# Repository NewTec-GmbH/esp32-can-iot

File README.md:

# ESP CAN-Analyzer
An ESP32 based interface between CAN-Bus and IoT environments.

This project has the main objective of interfacing a CAN Bus with the user through the use of the Lawicel Protocol (also known as SLCAN). Lawicel represents CAN Frames as strings of ASCII Symbols which can be easily interpreted by the user of by the numerous applications available online. 

- [Technical Specifications](#Technical-Specifications)
	- [Software Requirements](#Software-Requirements)
	- [Hardware Requirements](#Hardware-Requirements)
	- [Extra/Optional Requirements](#Extra/Optional-Requirements)
- [Context](#Context)
- [Use Case](#Use-Case)
- [Potential Optimization](#Potential-Optimization)
- [Specialized Pages](#Specialized-Pages)

# Technical Specifications 
## Software Requirements
* Support Standard and Extended frame formats
* WiFi Mode Selection (AP or STA)
* Support *Lawicel* Protocol
* HTTP Server over WiFi
* Server shall support authentication
* AP credentials changed through Server
* STA credentials changed through Server
* Bit Timing and Filters changed through Server
* CAN monitoring page (depending on available memory)
* Send CAN frame on demand
* Send CAN frame periodically
* CAN BUS Termination on Demand

## Hardware Requirements
* ESP32-based
* ISO 11898 Compliant (CAN up to 1 Mbps)
* CAN Bus Termination on Demand
* Support CAN through DSUB-9
* Support OBD through DSUB-9
* Bus-off State
* ISO 7637 compliant (Road vehicles -- Electrical disturbances from conduction and coupling)
* Control Button
* Red Error LED
* 4 GPIOs via Clamps

## Extra/Optional Requirements
* Identification of Error Message
* Reset through Webserver (Save and Restart)
* View OBD Messages (.dbc file?)
* LAWICEL over websocket/mqtt (to nodejs/node-red)

# Context

Based on the Lawicel Protocol, this project connects any standard CAN Bus to the user-end system. One example is its use on the Automotive Environment, where the CAN Bus is acquired through the DSUB-9 connector. The Frames are parsed through Lawicel into an ASCII String and sent through Serial to the Users Laptop. There is a second option, which is sending this String through a Websocket to the user. This enables the use of other IoT tools on the user's side, for example, Node-Red.

# Use Case

The use case for this project is based on the direct connection to a CAN Bus, in order to obtain the information being sent between the members of this bus. On the other side of this communication we find a Serial Interface or a Websocket Interface which presents the information to the user. The user has to provide the device with the characteristics of the Bus it is connected to, in order to correctly acquire the data.

# Potential Optimization

Thisproject has the potential to be improved in many of its aspects, specially its Firmware. These are some of the points that have been noted during the development, which can be improved in order to increase the performance:

* Lawicel commands active during AP Mode
* Use of Binary Lawicel Commands instead of Strings
* Optimize the Websocket Buffering of Messages (in both directions)
* Use of both Cores for Tasking
* Send Cyclic Frames using a Lawicel Command
* Prevent reset after car's start/stop

# Specialized Pages

* [Hardware](./Hardware/README.md)
* [Firmware](./Coding/fw/README.md)
	* [Documentation](./Coding/fw/doc/README.md)
	* [Libraries](./Coding/fw/lib/README.md)
		* [Lawicel Protocol](./Coding/fw/lib/Lawicel/README.md)
		* [CAN](./Coding/fw/lib/CAN/README.md)
	* [Application](./Coding/fw/src/README.md)
	* [Unit Test](./Coding/fw/test/README.md)
* [Glosary](./Coding/fw/doc/Glosary.md)

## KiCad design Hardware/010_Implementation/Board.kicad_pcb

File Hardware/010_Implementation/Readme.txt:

Circuit Diagram and Layout

Reyes, Gabryel
KiCad 5.1.6
Version 1 ------- 28.09.2020
Version 1.1 ----- 06.10.2020

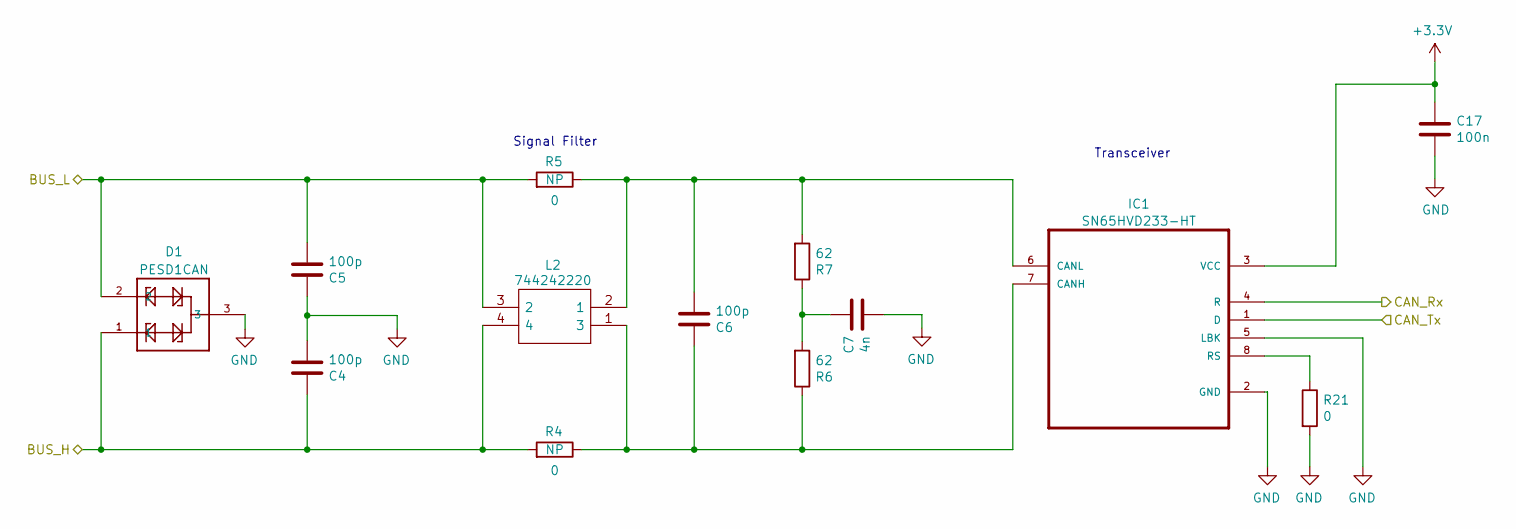
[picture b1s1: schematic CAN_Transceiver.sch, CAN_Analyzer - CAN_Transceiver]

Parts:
C4, C5, C6: 100p; C_0603_1608Metric_Pad1.08x0.95mm_HandSolder
C7: 4n; C_0603_1608Metric_Pad1.08x0.95mm_HandSolder
C17: 100n; C_0603_1608Metric_Pad1.08x0.95mm_HandSolder
D1: PESD1CAN; SOT23-3
IC1: SN65HVD233-HT; SOIC127P600X175
L2: 744242220; WE-SLM77; Mouser Part Number 710-744242220
R4, R5, R21: 0; R_0603_1608Metric_Pad0.98x0.95mm_HandSolder
R6, R7: 62; R_0603_1608Metric_Pad0.98x0.95mm_HandSolder

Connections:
+3V3: C17.1, IC1.3 (VCC); also elsewhere on the board
/CAN_Transceiver/BUS_H: C4.1, D1.1, L2.4, R4.2; also elsewhere on the board
/CAN_Transceiver/BUS_L: C5.2, D1.2, L2.3 (2), R5.2; also elsewhere on the board
/CAN_Transceiver/CAN_Rx: IC1.4 (R); also elsewhere on the board
/CAN_Transceiver/CAN_Tx: IC1.1 (D); also elsewhere on the board
GND: C4.2, C5.1, C7.2, C17.2, D1.3, IC1.2 (GND), IC1.5 (LBK), R21.2; also elsewhere on the board
unnamed: C6.1, IC1.7 (CANH), L2.1 (3), R4.1, R6.1
unnamed: C6.2, IC1.6 (CANL), L2.2 (1), R5.1, R7.2
unnamed: C7.1, R6.2, R7.1
unnamed: IC1.8 (RS), R21.1

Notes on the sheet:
Transceiver
Signal Filter

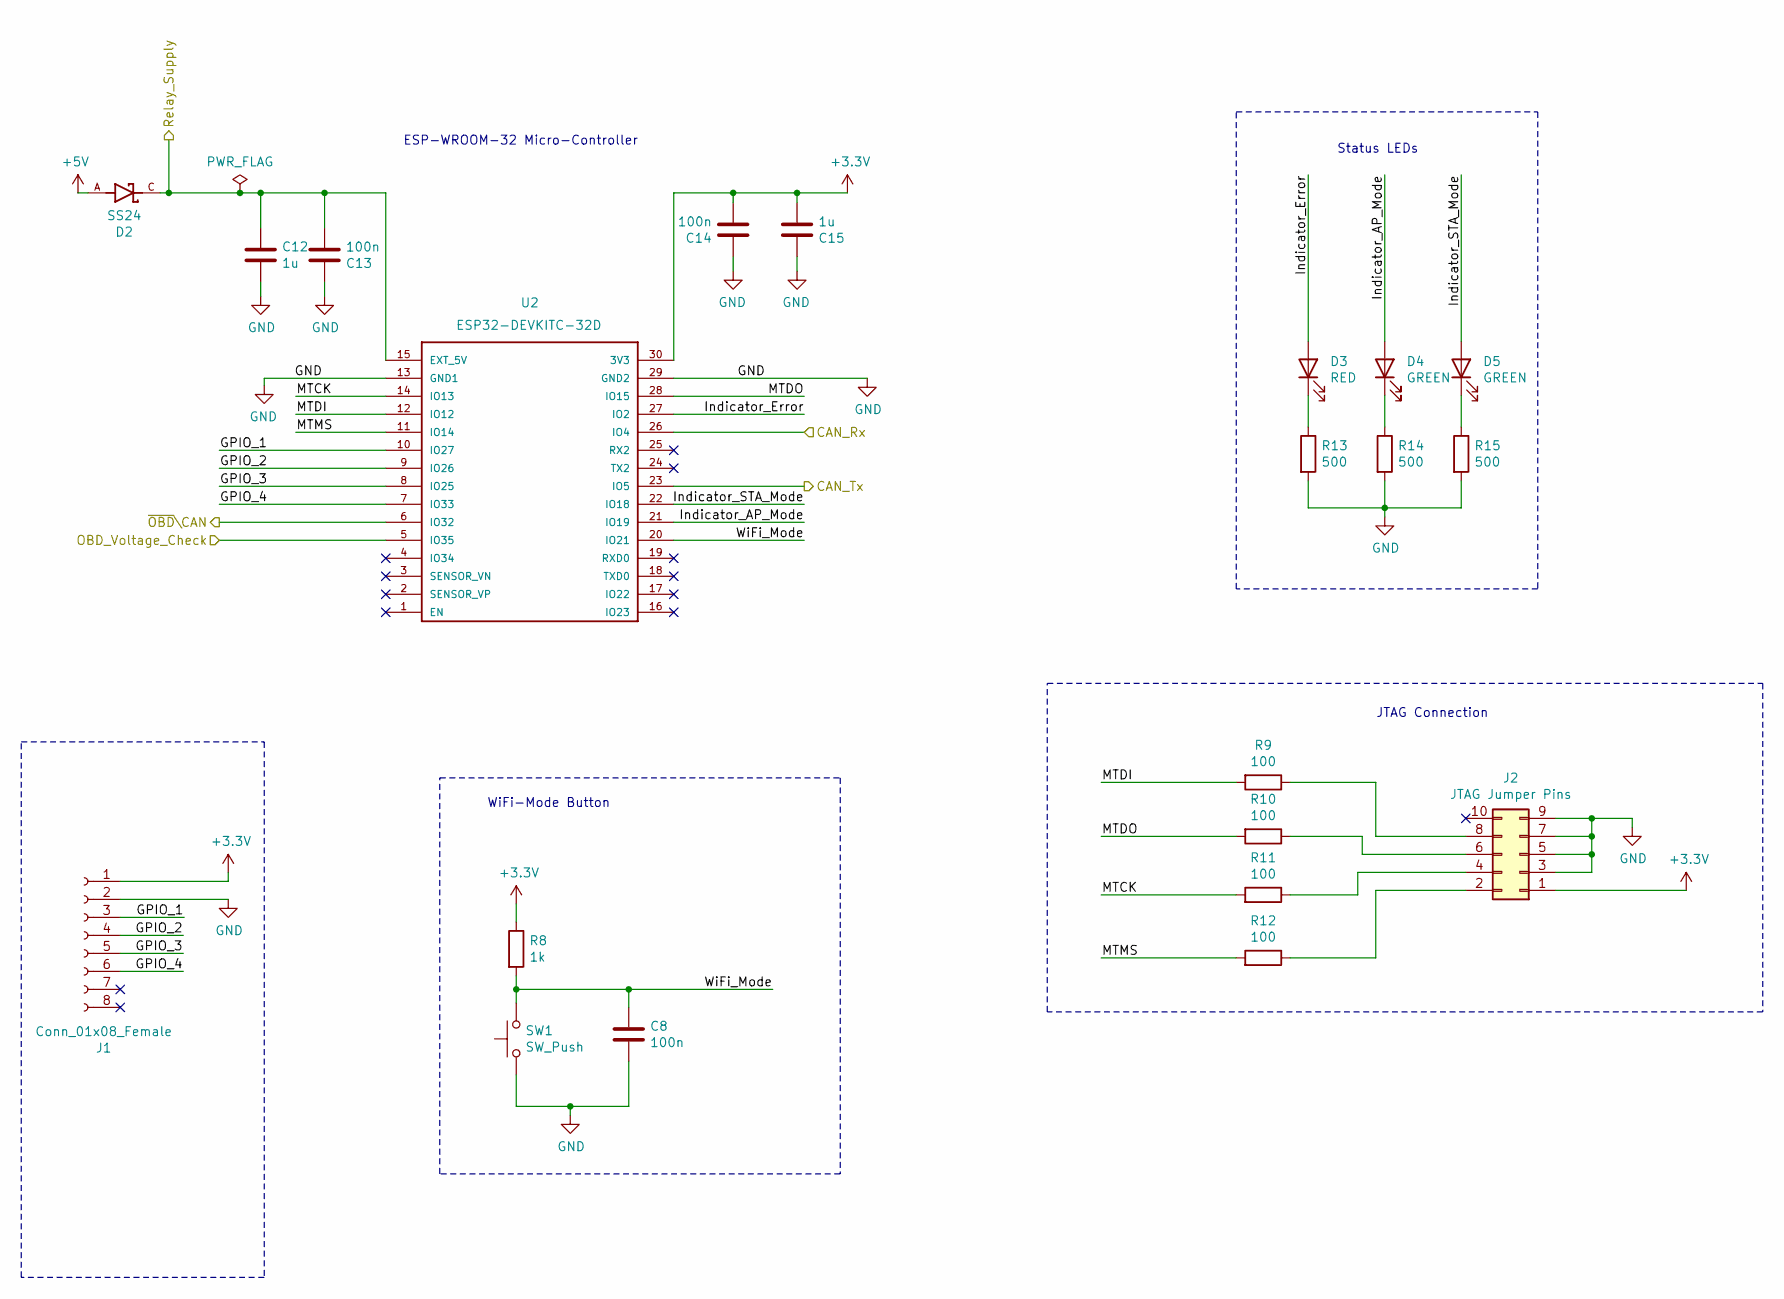
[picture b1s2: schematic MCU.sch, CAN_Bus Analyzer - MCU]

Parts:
C8, C13, C14: 100n; C_0603_1608Metric_Pad1.08x0.95mm_HandSolder
C12, C15: 1u; C_0603_1608Metric_Pad1.08x0.95mm_HandSolder
D2: SS24; DIOM5336X265N
D3: RED; LED_D3.0mm
D4, D5: GREEN; LED_D3.0mm
J1: Conn_01x08_Female; AST 045-08
J2: JTAG Jumper Pins; PinHeader_2x05_P1.00mm_Vertical
R8: 1k; R_0603_1608Metric_Pad0.98x0.95mm_HandSolder
R9, R10, R11, R12: 100; R_0603_1608Metric_Pad0.98x0.95mm_HandSolder
R13, R14, R15: 500; R_0603_1608Metric_Pad0.98x0.95mm_HandSolder
SW1: SW_Push; SW_Push_1P1T_NO_CK_KSC7xxJ
U2: ESP32-DEVKITC-32D; MODULE_ESP32-DEVKITC-32D

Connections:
+3V3: C14.2, C15.2, J1.1, J2.1, R8.1, U2.30 (3V3); also elsewhere on the board
+5V: D2.A; also elsewhere on the board
/CAN_Transceiver/CAN_Rx: U2.26 (IO4); also elsewhere on the board
/CAN_Transceiver/CAN_Tx: U2.23 (IO5); also elsewhere on the board
/Connector/Relay_Supply: C12.1, C13.2, D2.C, U2.15 (EXT_5V); also elsewhere on the board
/Connector/~OBD~\CAN: U2.6 (IO32); also elsewhere on the board
/MCU/GPIO_1: J1.3, U2.10 (IO27)
/MCU/GPIO_2: J1.4, U2.9 (IO26)
/MCU/GPIO_3: J1.5, U2.8 (IO25)
/MCU/GPIO_4: J1.6, U2.7 (IO33)
/MCU/Indicator_AP_Mode: D4.2 (A), U2.21 (IO19)
/MCU/Indicator_Error: D3.2 (A), U2.27 (IO2)
/MCU/Indicator_STA_Mode: D5.2 (A), U2.22 (IO18)
/MCU/MTCK: R11.2, U2.14 (IO13)
/MCU/MTDI: R9.2, U2.12 (IO12)
/MCU/MTDO: R10.2, U2.28 (IO15)
/MCU/MTMS: R12.2, U2.11 (IO14)
/MCU/OBD_Voltage_Check: U2.5 (IO35); also elsewhere on the board
/MCU/WiFi_Mode: C8.1, R8.2, SW1.2, U2.20 (IO21)
GND: C8.2, C12.2, C13.1, C14.1, C15.1, J1.2, J1.7, J1.8, J2.3, J2.5, J2.7, J2.9, R13.2, R14.2, R15.2, SW1.1, U2.13 (GND1), U2.29 (GND2); also elsewhere on the board
unnamed: D3.1 (K), R13.1
unnamed: D4.1 (K), R14.1
unnamed: D5.1 (K), R15.1
unnamed: J2.2, R12.1
unnamed: J2.4, R11.1
unnamed: J2.6, R10.1
unnamed: J2.8, R9.1

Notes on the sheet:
ESP-WROOM-32 Micro-Controller
Status LEDs
WiFi-Mode Button
JTAG Connection

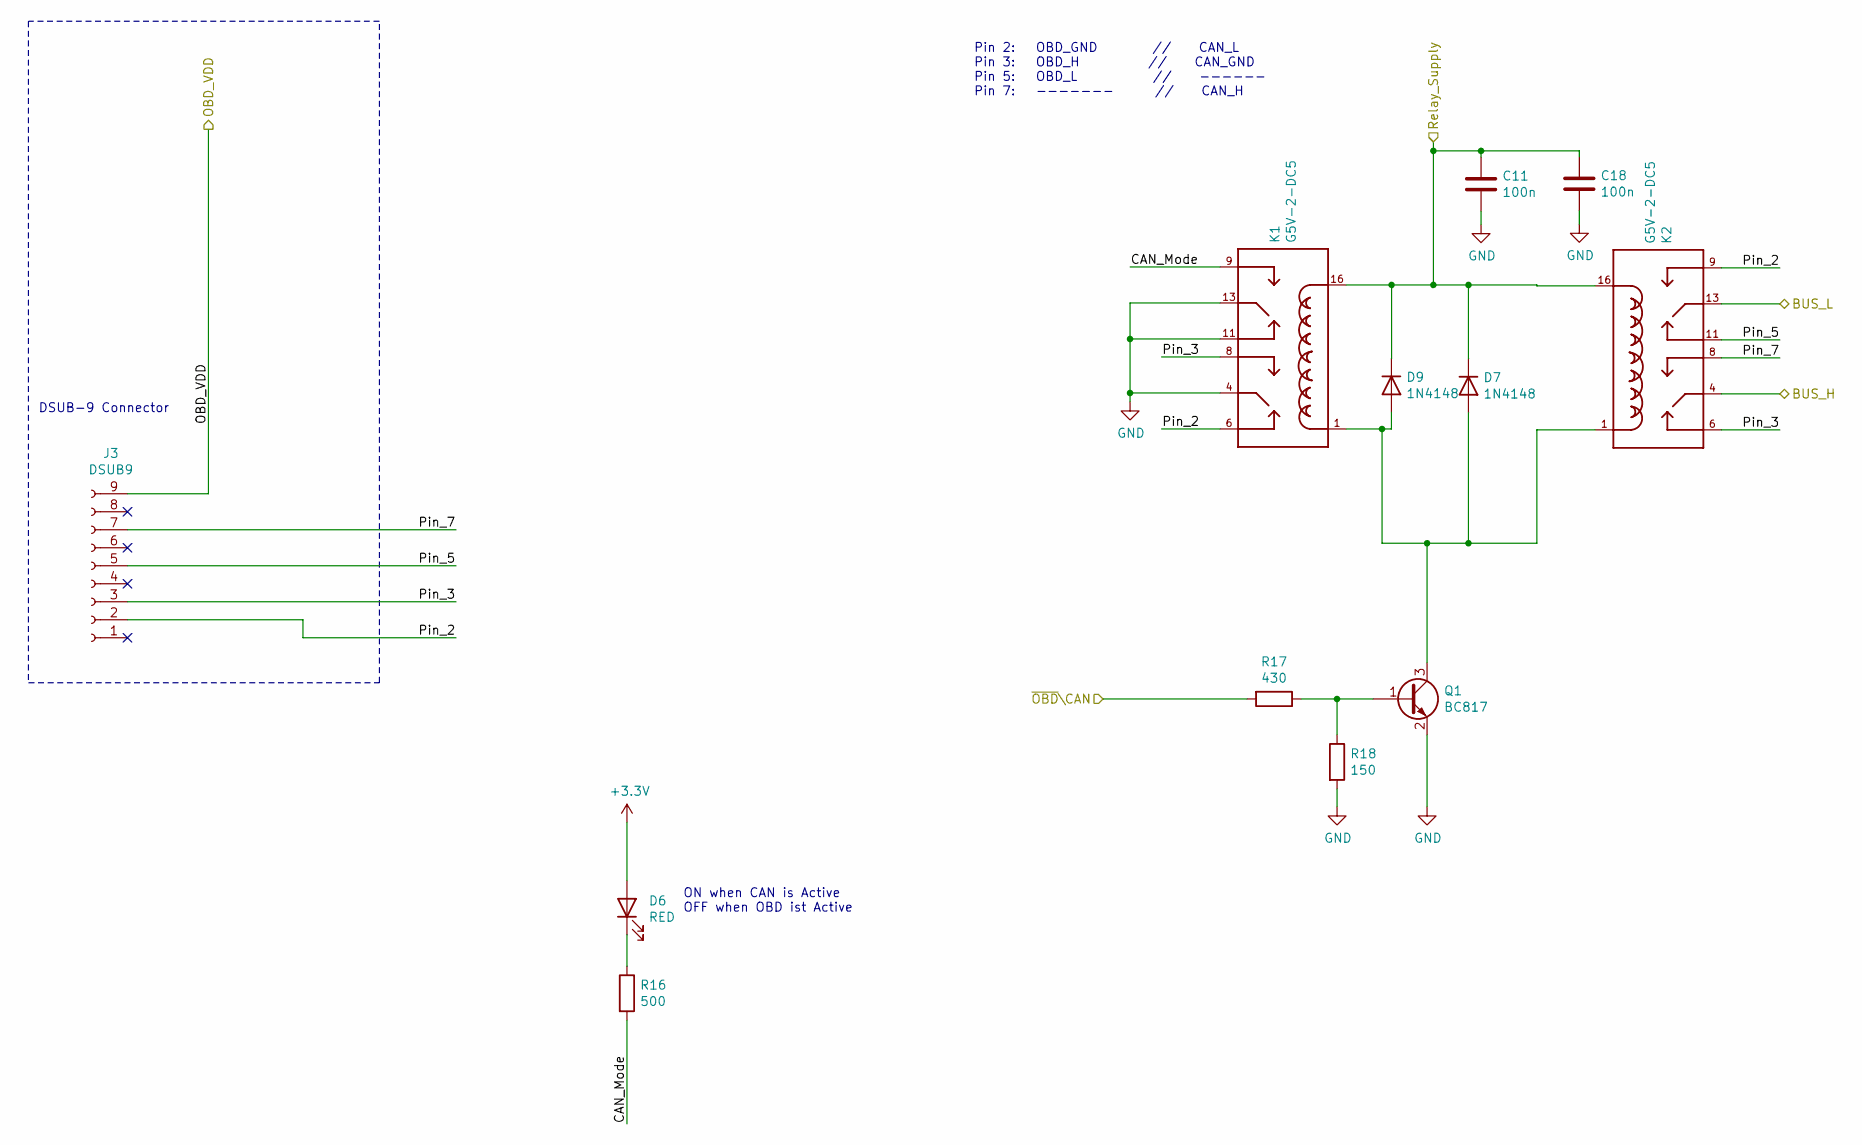
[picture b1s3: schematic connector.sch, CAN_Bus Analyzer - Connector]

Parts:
C11, C18: 100n; C_0603_1608Metric_Pad1.08x0.95mm_HandSolder
D6: RED; LED_D3.0mm
D7, D9: 1N4148; D_DO-35_SOD27_P7.62mm_Horizontal
J3: DSUB9; DSUB-9_Male_Horizontal_P2.77x2.84mm_EdgePinOffset4.94mm_Hou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
K1, K2: G5V-2-DC5; RELAY_G5V-2-DC5
Q1: BC817; SOT-23
R16: 500; R_0603_1608Metric_Pad0.98x0.95mm_HandSolder
R17: 430; R_0603_1608Metric_Pad0.98x0.95mm_HandSolder
R18: 150; R_0603_1608Metric_Pad0.98x0.95mm_HandSolder

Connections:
+3V3: D6.2 (A); also elsewhere on the board
/CAN_Transceiver/BUS_H: K2.4; also elsewhere on the board
/CAN_Transceiver/BUS_L: K2.13; also elsewhere on the board
/Connector/CAN_Mode: K1.9, R16.2
/Connector/OBD_VDD: J3.9; also elsewhere on the board
/Connector/Pin_2: J3.2, K1.6, K2.9
/Connector/Pin_3: J3.3, K1.8, K2.6
/Connector/Pin_5: J3.5, K2.11
/Connector/Pin_7: J3.7, K2.8
/Connector/Relay_Supply: C11.1, C18.1, D7.1 (K), D9.1 (K), K1.16, K2.16; also elsewhere on the board
/Connector/~OBD~\CAN: R17.2; also elsewhere on the board
GND: C11.2, C18.2, K1.4, K1.11, K1.13, Q1.2 (E), R18.2; also elsewhere on the board
unnamed: D6.1 (K), R16.1
unnamed: D7.2 (A), D9.2 (A), K1.1, K2.1, Q1.3 (C)
unnamed: Q1.1 (B), R17.1, R18.1

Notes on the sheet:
DSUB-9 Connector
Pin 2: OBD_GND // CAN_L Pin 3: OBD_H // CAN_GND Pin 5: OBD_L // ------ Pin 7: ------- // CAN_H
ON when CAN is Active OFF when OBD ist Active

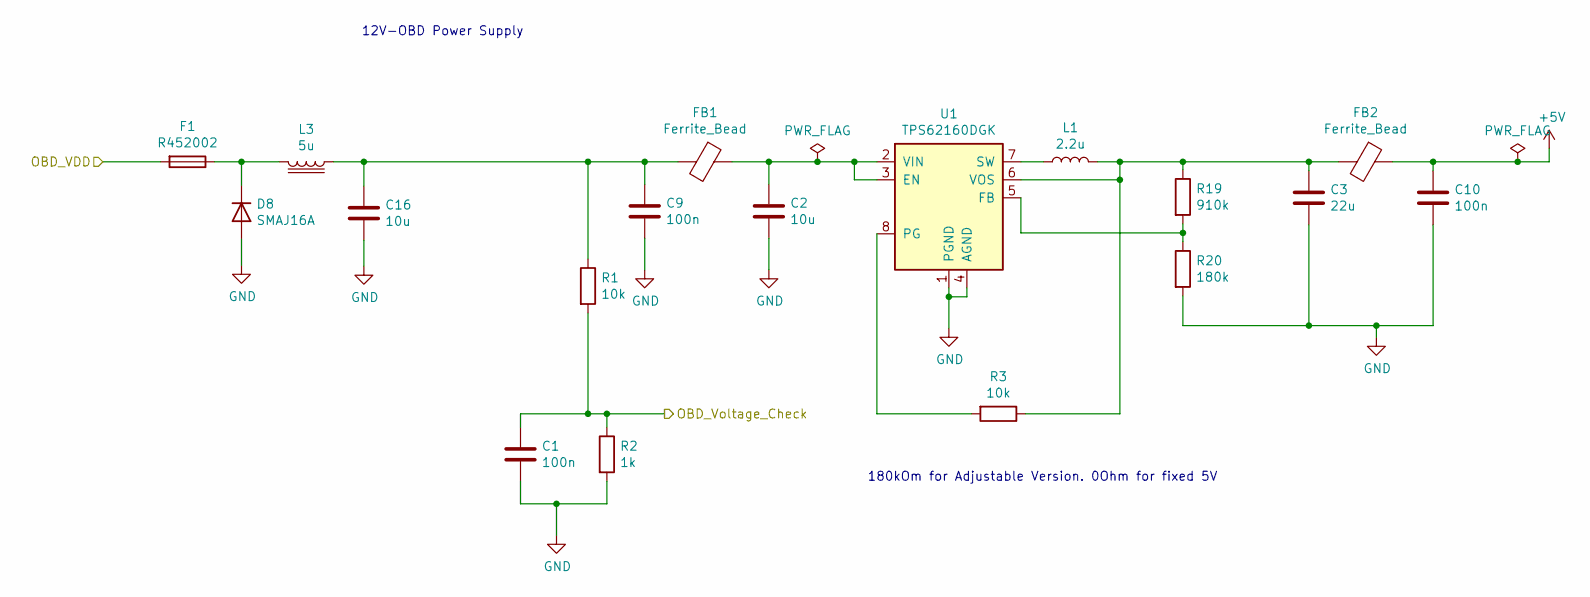
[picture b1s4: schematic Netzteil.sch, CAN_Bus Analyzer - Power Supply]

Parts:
C1, C9, C10: 100n; C_0603_1608Metric_Pad1.08x0.95mm_HandSolder
C2, C16: 10u; C_1206_3216Metric_Pad1.33x1.80mm_HandSolder
C3: 22u; C_1206_3216Metric_Pad1.33x1.80mm_HandSolder
D8: SMAJ16A; D_SMA
F1: R452002; Fuse_2512_6332Metric_Pad1.52x3.35mm_HandSolder
FB1, FB2: Ferrite_Bead; L_0603_1608Metric_Pad1.05x0.95mm_HandSolder
L1: 2.2u; INDPM5550X300N
L3: 5u; INDPM5550X300N
R1, R3: 10k; R_0603_1608Metric_Pad0.98x0.95mm_HandSolder
R2: 1k; R_0603_1608Metric_Pad0.98x0.95mm_HandSolder
R19: 910k; R_0603_1608Metric_Pad0.98x0.95mm_HandSolder
R20: 180k; R_0603_1608Metric_Pad0.98x0.95mm_HandSolder
U1: TPS62160DGK; VSSOP-8_3.0x3.0mm_P0.65mm

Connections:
+5V: C10.1, FB2.1; also elsewhere on the board
/Connector/OBD_VDD: F1.2; also elsewhere on the board
/MCU/OBD_Voltage_Check: C1.1, R1.2, R2.1; also elsewhere on the board
GND: C1.2, C2.2, C3.2, C9.2, C10.2, C16.2, D8.2 (A), R2.2, R20.2, U1.1 (PGND), U1.4 (AGND); also elsewhere on the board
unnamed: C2.1, FB1.1, U1.2 (VIN), U1.3 (EN)
unnamed: C3.1, FB2.2, L1.2, R3.1, R19.1, U1.6 (VOS)
unnamed: C9.1, C16.1, FB1.2, L3.1, R1.1
unnamed: D8.1 (K), F1.1, L3.2
unnamed: L1.1, U1.7 (SW)
unnamed: R3.2, U1.8 (PG)
unnamed: R19.2, R20.1, U1.5 (FB)

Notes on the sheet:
12V-OBD Power Supply
180kOm for Adjustable Version. 0Ohm for fixed 5V

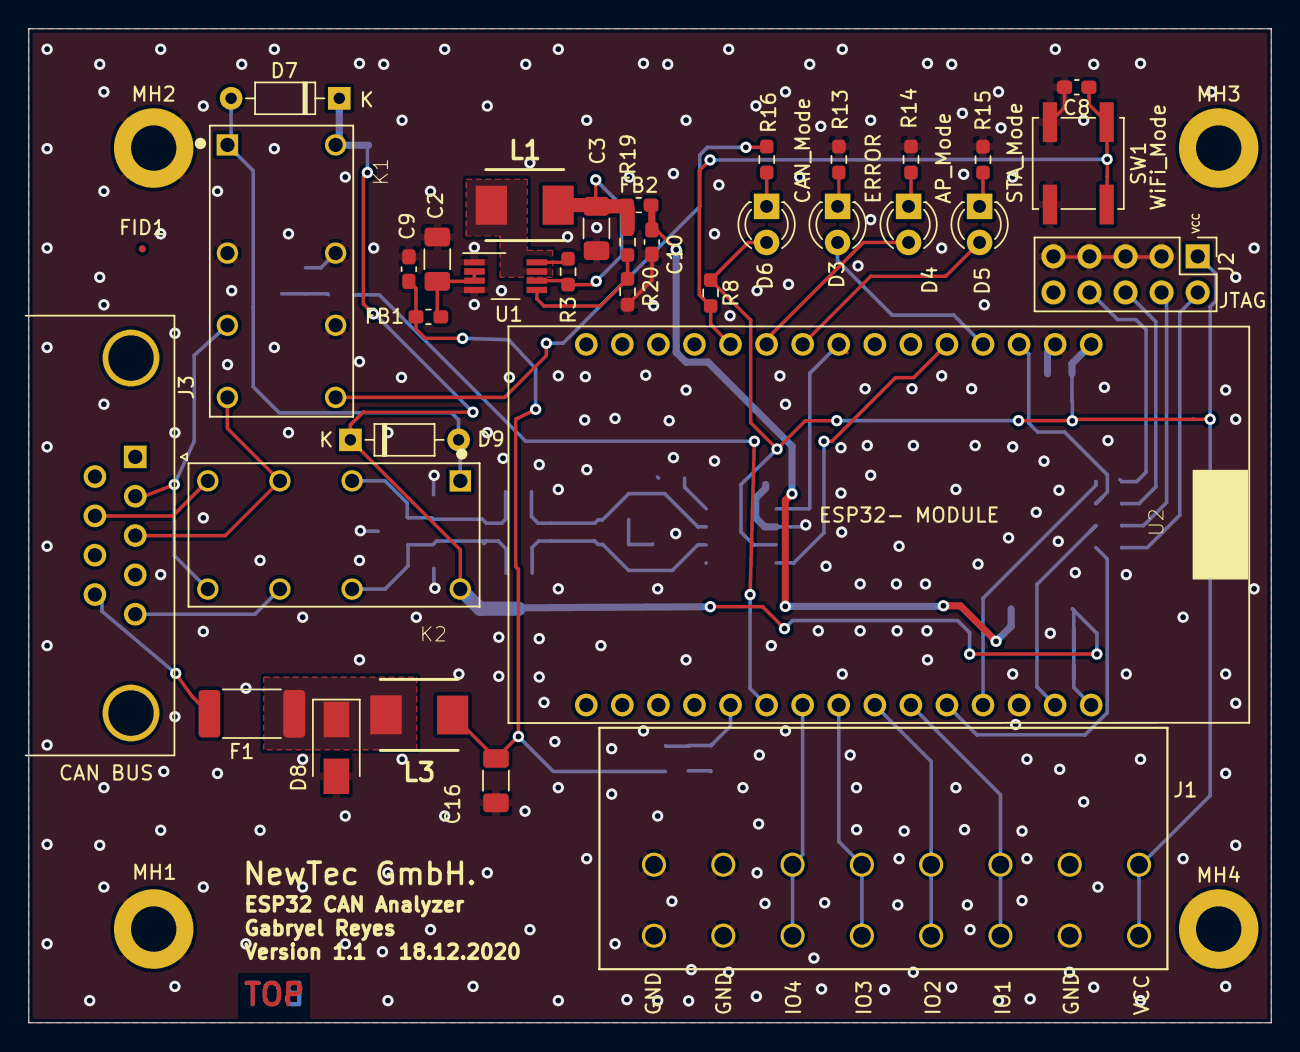
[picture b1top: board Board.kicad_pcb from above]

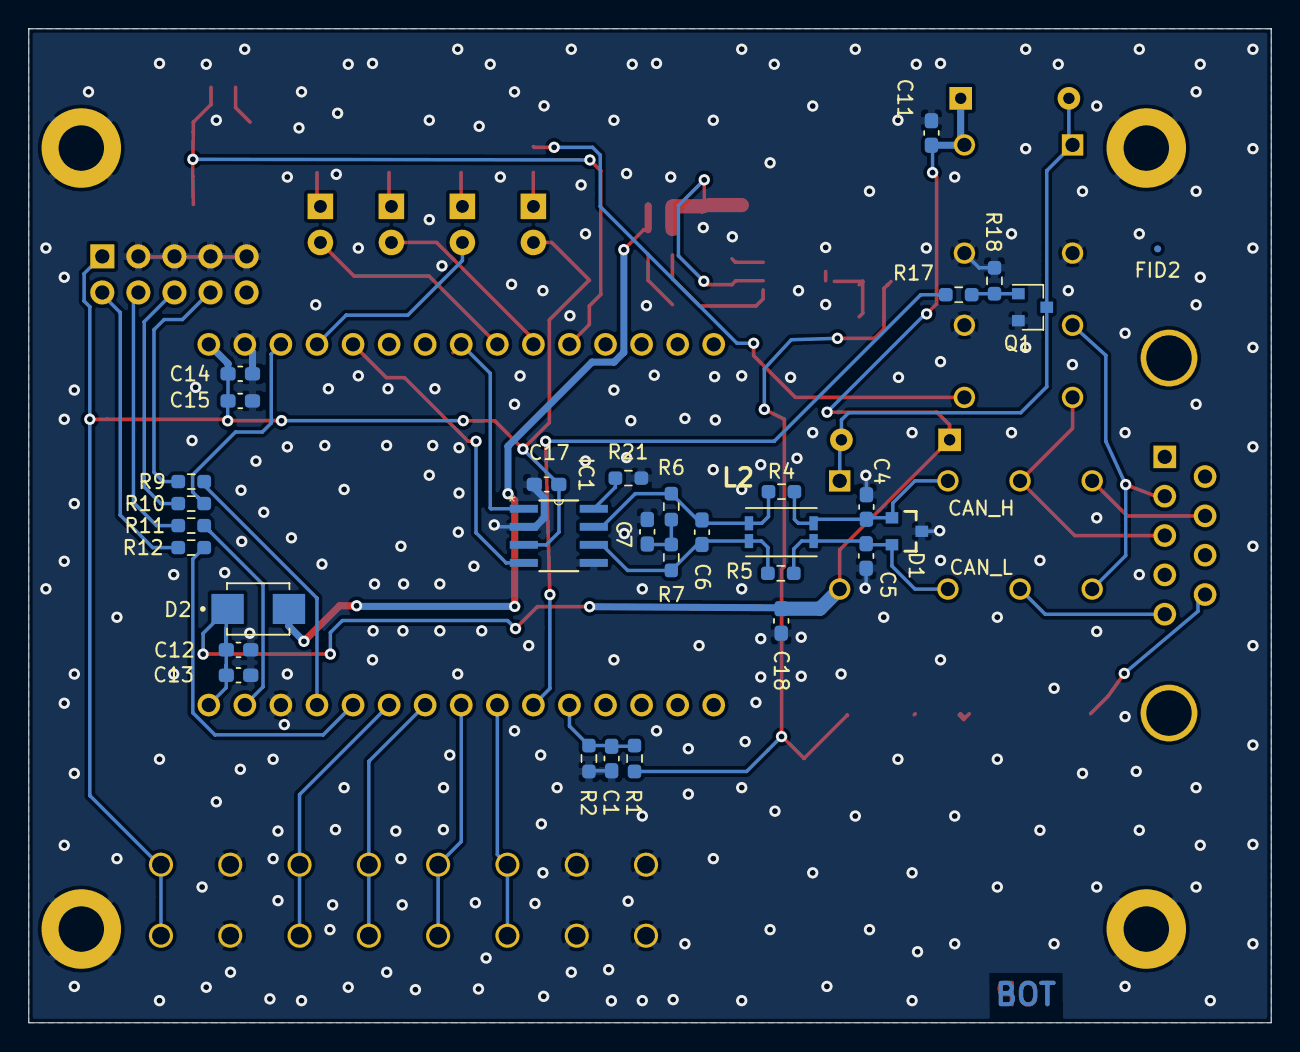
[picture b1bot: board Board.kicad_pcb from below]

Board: 2 copper layers, 87.5 x 70.0 mm, 70 parts (31 on the bottom side), 49 nets.

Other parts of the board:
FID1, FID2: Fiducial_0.5mm_Mask1mm
MH1, MH2, MH3, MH4: MountingHole_3.2mm_M3_DIN965_Pad

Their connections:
GND: MH1.1, MH2.1, MH3.1, MH4.1; also elsewhere on the board

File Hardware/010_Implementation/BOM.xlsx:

Id | Designator | Package | Quantity | Designation | NewTec | Digikey
1 | REF**,REF**,REF** | MountingHole_3.2mm_M3_DIN965_Pad | 3 | MountingHole_3.2mm_M3_DIN965_Pad | X
2 | J1 | AST 045-08 | 1 | Conn_01x08_Female | X
3 | K2,K1 | RELAY_G5V-2-DC5 | 2 | G5V-2-DC5 |  | X
5 | L1 | INDPM5550X300N | 1 | 2.2u | X |  |  |  | https://www.digikey.de/short/zv370m
6 | L3 | INDPM5550X300N | 1 | 5u | X
7 | U1 | VSSOP-8_3.0x3.0mm_P0.65mm | 1 | TPS62160DGK |  | X
8 | R21,R5,R4 | R_0603_1608Metric_Pad0.98x0.95mm_HandSolder | 3 | 0 | X
9 | R20 | R_0603_1608Metric_Pad0.98x0.95mm_HandSolder | 1 | 180k | X
10 | R19 | R_0603_1608Metric_Pad0.98x0.95mm_HandSolder | 1 | 953k | X
11 | R18 | R_0603_1608Metric_Pad0.98x0.95mm_HandSolder | 1 | 150 | X
12 | R17 | R_0603_1608Metric_Pad0.98x0.95mm_HandSolder | 1 | 430 | X
13 | R16,R15,R14,R13 | R_0603_1608Metric_Pad0.98x0.95mm_HandSolder | 4 | 500 | X
14 | R12,R11,R10,R9 | R_0603_1608Metric_Pad0.98x0.95mm_HandSolder | 4 | 100 | X
15 | R8,R2 | R_0603_1608Metric_Pad0.98x0.95mm_HandSolder | 2 | 1k | X
16 | R7,R6 | R_0603_1608Metric_Pad0.98x0.95mm_HandSolder | 2 | 62 | X
17 | R3,R1 | R_0603_1608Metric_Pad0.98x0.95mm_HandSolder | 2 | 10k | X
18 | C15,C12 | C_0603_1608Metric_Pad1.08x0.95mm_HandSolder | 2 | 1u | X
19 | C17, C14,C13,C11,C10,C9,C8,C1 | C_0603_1608Metric_Pad1.08x0.95mm_HandSolder | 7 | 100n | X
20 | C7 | C_0603_1608Metric_Pad1.08x0.95mm_HandSolder | 1 | 4n | X
21 | C6,C5,C4 | C_0603_1608Metric_Pad1.08x0.95mm_HandSolder | 3 | 100p | X
22 | FB2,FB1 | L_0603_1608Metric_Pad1.05x0.95mm_HandSolder | 2 | Ferrite_Bead | X
23 | C16,C2 | C_1206_3216Metric_Pad1.33x1.80mm_HandSolder | 2 | 10u | X
24 | C3 | C_1206_3216Metric_Pad1.33x1.80mm_HandSolder | 1 | 22u | X
25 | F1 | Fuse_2512_6332Metric_Pad1.52x3.35mm_HandSolder | 1 | R452002 | X
26 | D8 | D_SMA | 1 | SMAJ16A | X
27 | L2 | WE-SLM77 | 1 | 744242220 |  | X
28 | U2 | MODULE_ESP32-DEVKITC-32D | 1 | ESP32-DEVKITC-32D | X
29 | Q1 | SOT-23 | 1 | BC817 | X
30 | D7 | D_DO-35_SOD27_P7.62mm_Horizontal | 1 | 1N4148 | X
31 | D6,D3 | LED_D3.0mm | 2 | RED | X
32 | D2 | DIOM5336X265N | 1 | SS24 | X
33 | SW1 | SW_Push_1P1T_NO_CK_KSC7xxJ | 1 | SW_Push |  | X
34 | J3 | DSUB-9_Female_Horizontal_P2.77x2.84mm_EdgePinOffset4.94mm_Housed_MountingHolesO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 | 1 | DSUB9 |  | X
35 | J2 | PinHeader_2x05_P1.00mm_Vertical | 1 | JTAG Jumper Pins |  | X
36 | IC1 | SOIC127P600X175 | 1 | SN65HVD233-HT |  | X
37 | D5,D4 | LED_D3.0mm | 2 | GREEN | X
38 | D1 | SOT23-3 | 1 | PESD1CAN | X

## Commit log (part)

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2020-10-27 Optimized help functions. Implemented the bool return types with the correct logic. Corrected bool returns in Lawicel and CAN Int./Adap. so far
2020-10-28 Finished changing Bool return types. Program doesnt work
2020-10-28 Changed bugged returns in CAN and NVM.
2020-10-28 Send frame fixed: send only when success starting frame
2020-10-28 Fixed Indentation
2020-10-28 Directoy defined as constant. For performance and reliability
2020-10-29 Updated Schematic. Fixed Connection to Ground to prevent Software Bugs
2020-10-29 Added Mainloop sequence diagram. Changed return type in serial process diag.
2020-10-29 Moved adapters to a folder
2020-10-29 Defines methods on Settings.h
2020-10-30 implemented Settings class. NVMadapter modified for it
2020-10-30 Added IO and Board Classes
2020-11-02 IO Pins implemented and initialized in main
2020-11-03 Added Schotlly Diode, PDF and autorouted Vias
2020-11-03 Implemented Debouncing for WiFi Mode button
2020-11-03 created Webpages Navigation UML Diagramm
2020-11-03 Updated UML Diagramm
2020-11-04 Webserverclass UML Diagram added
2020-11-04 Settings Class as namespace implemented. NVMAdapter and Main adapted to this change.
2020-11-04 Webconfig implemented
2020-11-04 Implemented init() and begin() in ESP_server.
2020-11-04 implemented save and import confign in WebConfig. Pages adapted to fit this changes
2020-11-04 Captive Portal namespace defined
2020-11-04 Credentials Configuration moved to Captive Portal. Configuration of Captive Portal implemented
2020-11-04 Fixed the storing and calling of credentials
2020-11-05 Serving static files in CP mode
2020-11-05 Fixed CS for ESP_Server
2020-11-06 POST Method implemented
2020-11-09 PCB Updated
2020-11-09 Added comments for Documentation
2020-11-09 Fixed displaying of webpage. Before was a testing messages
2020-11-10 Board version 4.1
2020-11-10 Captive Portal responses fixed. New Credentials are stored and correctly called. InitPages implemented as local method
2020-11-10 Deleted extra column
2020-11-11 Board Version 4.2
2020-11-12 Board Version 5
2020-11-12 Error LED in Main implementiert
2020-11-17 Readme.md layout written as guide
2020-11-17 Added State Machine to ReadMe
2020-11-19 Wrote Architecture in Readme and fixed Diagrams
2020-11-23 Board Version 6
2020-11-24 Added Anchor points to PCB
2020-11-24 Moved Pi-Filter to the top section. Added alignment marks on the back layer.
2020-11-25 Board version 8 with gerber files
2020-11-26 Updated BOM
2020-11-27 Websocket Namespace implemented
2020-11-27 Websocket Adapter for Lawicel implemented
2020-11-30 Linked WS Webpage to index
2020-11-30 Styled index.html
2020-11-30 deleted w3.css
2020-11-30 Passed Directory as reference. Commented each argument of methods.
2020-11-30 Renamed setXXX into getXXX
2020-12-01 Added comments and header in Web_config
2020-12-01 webserver as class private static in header file
2020-12-01 Halt function implemented. Resstart called from Board
2020-12-01 MIT Licence for IO and Board Classes
2020-12-01 Removed Debugging elements
2020-12-01 Separated isRestartRequested and handleCycle
2020-12-01 Added Licence to HTML files
2020-12-01 Board Version 1.0 Review 5
2020-12-02 Board Version 1.0 Review 6
2020-12-02 Added missing bool returns
2020-12-02 Added Serial.begin to Websocket for debugging
2020-12-03 Implemented System Timestamp
2020-12-07 WebServer in Cpp as static defined
2020-12-07 Typo in webconfig
2020-12-08 Fixed missing leading Zeroes in Frame Data bytes
2020-12-09 Added missing comments in Pages.cpp
2020-12-09 Fixed Typo in Web_Config Enum StatusCodes
2020-12-09 fixed incorrect return type
2020-12-09 changed sintax to improve reading
2020-12-09 implemented receive in Websocket
2020-12-09 Fixed details missing after merging
2020-12-10 Implemented receive message from Websocket
2020-12-10 Send Text command from webpage to Lawicel
2020-12-13 CAN Frame from Webpage implemented
2020-12-16 Fixed message sending from website
2020-12-16 Modified CAN tx and rx Pins to fit the Hardware
2020-12-16 Implemented getIPAddress It displays Server IP address on Serial Monitor
2020-12-16 Fixed CANAdapter false return when sending frame
2020-12-17 Fixed sending frames with DLC=0
2020-12-17 Imported CAN Library to Project Lib.
2020-12-17 Return = -1 Fix Documented
2020-12-17 Optimized send buttons in webpage
2020-12-17 Separated WLAN connection from WebServer. Refactoring of all components dependant on WiFi connection
2020-12-17 moved Websocket init to Pages init
2020-12-17 Fixed send on enter on website
2020-12-18 Static serving correct files in Captive Portal
2020-12-18 Fixed Style of Captive Portal Message
2021-01-07 Fixed terminator for BEL in JS
2021-01-07 WebSocket UML Diagram
2021-01-07 Use Case UML Diagrams
2021-01-07 Fixed terminator for BEL in JS using HEX
2021-01-07 Request Status LED in WS implemented
2021-01-08 Added favicon
2021-01-08 Autofocus on Command Input Box for ws
2021-01-08 Fixed leading zero in Data Payload. Missing Zero when Data between 0x0A and 0x0F
2021-01-08 Auto PID Analysis in JS implemented
2021-01-11 Deleted extra gauge line from js
2021-01-11 Added missing Comments
2021-01-11 setFiltermode Implemented. Constructor updated for use of Filters
2021-01-11 Implemented setAMn
2021-01-11 Fixed bug in setAMnCmd. Missing ! in if statements
2021-01-12 Defined functions for the use of Hardware CAN Filters
2021-01-12 Implemented Filter Mode in Hardware Filter
2021-01-12 Changd Filter Data Type into struct
2021-01-13 OPD not passed as constant reference
2021-01-13 Refactoring of readWifiMode
2021-01-13 Websocket sent message passed as const reference.
2021-01-13 Changed getTimestamp for getFormattedTimestamp. Format is adjusted for Lawicel Protocol
2021-01-13 Board: Yoda Notation in IF-statements
2021-01-13 WebServer: Yoda Notation in IF-statements
2021-01-13 Adapters: Yoda Notation in IF-statements
2021-01-13 Ordered and Commented JavaScript
2021-01-13 JS: Yoda Notation in IF-statements
2021-01-13 Updated Doxyfile
2021-01-13 Added CAN lib to Exclusions in Doxyfile
2021-01-13 IP Address returned as const reference
2021-01-13 Deleted unused Defines
2021-01-13 Added isEmpty Method for Tests
2021-01-13 Prepared Test Adapters
2021-01-14 Software Fixed for Hardware Version 1.1
2021-01-14 Changed Magic number for constant
2021-01-14 Deleted useless commented Code
2021-01-14 Changed Timeout of Websocket Queue. Error handling in case of Full Queue
2021-01-15 Fixed Format in Comment
2021-01-15 Added error blink when receive Queue is full
2021-01-15 Deleted unused Filter code
2021-01-15 Fixed Bug: System Crash on AP_Mode. Caused by uninitialized Websocket Queue
2021-01-15 Fixed Native environment for testing
2021-01-15 Changed return type in copyFrame
2021-01-15 Unit Tests: Succesfully testet until Close Channel
2021-01-18 Tested until tx_ext_rtr
2021-01-18 Tested Lawicel Protocol (no NVM) Except functions with NVM Adapter.
2021-01-18 Implemented test_nvm
2021-01-18 Coding Style for TestMain
2021-01-18 Test ReadMe File updated
2021-01-18 CS for Test_Can_Adapter
2021-01-21 Separated Read me Files into Hardware and Software
2021-01-21 Rename HARDWARE.md to README.md
2021-01-21 Added Lawicel Protocol Documentation
2021-01-22 Deleted m_ prefix, and added static to IPAddress
2021-01-22 src folder ReadMe File. Deleted useless line in main
2021-01-22 Lawicel Protocol ReadMe
2021-01-25 Added Media Folder for explanatory Pictures
2021-01-25 Renamed Pictures
2021-01-25 Added DataFlow Diagram
2021-01-25 Added explanatory Diagram
2021-01-25 Added Read Me File for doc Folder
2021-01-25 Added Glosary
2021-01-25 Updated Sequence Diagram
2021-01-25 Minor visual changes on sequence diagram
2021-01-25 Updated Lawicel UML Diagram
2021-01-25 Renamed WSAdapter into WebSocketAdapter
2021-01-25 Deleted Implementation in FW Readme
2021-01-25 Updated Main Application Docs and diagrams
2021-01-25 Updated Websocket Documentation
2021-01-25 Added Example to test ReadMe
2021-01-25 Updated lib ReadMe
2021-01-25 Updated Glosary
2021-01-25 Fixed naming in Lawicel UML Diagram
2021-01-25 Fixed broken Link specialized pages
2021-01-26 Added Link to Lawicel Protocol from Libs
2021-01-27 Deleted useless line
2021-01-27 Added initializer for ODB switch GPIO
2021-01-27 Deleted useless Links in doc/ReadMe
2021-01-27 Added installation instructions to Test ReadMe
2021-01-28 Fixed Diagram Arrows
2021-01-28 Deleter unnecesary _h in Class diagram
2021-01-28 Deleted Use labels
2021-01-29 Added Node-Red Folder, flows and ReadMe
2021-01-29 Added PCB models
2021-01-29 Deleted PIDs txt description
2021-01-29 Added Frame Polling in Interaction Diag.
2021-02-01 Added 3D Models of Board and Casing
2021-02-01 Interaction Diagram Updated
2021-02-01 Updated Potential Optimization
2021-02-01 Added parser for buffered incoming frames
2021-02-01 Updated JS and Webpages for Websocket buffering
2021-02-01 Updated hardware ReadMe with Version 1.0
2021-02-01 Added explanation of Smart Switching
2021-02-02 Changed name of sendBuffer websocket method
2021-02-02 Changed compiler optimization flags
2021-02-03 Deleted useless String
2021-02-03 Added prevent start/stop to optimizations
2021-02-03 Fixed arrow. Dependency on Arduino
2021-02-03 Clear string buffer method in Lawicel
2021-02-03 Updated Interactions Diagram
2021-02-03 Re-implementation of interactions Diagram
2021-02-03 Changed Resistor values on voltage regulator
2021-02-04 Changed Asynchron Arrow for Client in interactions diagram
2021-02-12 Changed images to prevent copyright issues
2021-02-16 Changed Illustrations for Clipart
2021-02-23 Update LICENSE
2021-02-25 #14 Added missing Keyword "static" on local functions. Fixed Coding Style for function names
2021-02-25 #13 Fixed Coding Style for variable names.
2021-02-25 #7 Prevent assignment of value to "result" in case of error.
2021-02-25 #9 Default values passed as reference
2021-02-25 #10 Fixed Indentation and Doxygen Style in Lawicel
2021-02-25 #10 Fixed Indentation and Doxygen Style in Settings
2021-02-25 #10 Fixed Indentation and Doxygen Style in Adapters
2021-02-25 #10 Fixed Indentation and Doxygen Style in Test Adapters
2021-02-25 #15 Fixed unmatched file name with Doxygen Documentation
2021-02-26 #11 Fixed all Doxygen Warnings
2021-02-26 Deleted configuration for Hardware 1.0 (obsolete)
2021-06-18 #16 Added "u" sufix to unsigned constant
2021-06-18 #16 Fixed Doxygen style findings.
2021-11-04 Added OTA
2022-02-27 Automatic AP activation for Hardware V2, instead of going into fatal error wehn not able to connect to saved SSID
2023-01-20 The platform espressif32 fixed to v5.3.0
2023-01-20 Fixed dependencies, include paths and test framework.
2023-01-29 Updated gitignore
2023-01-29 Removed local CAN Library. Changed for a Github Repository
2023-01-29 Removed local Lawicel library. Changed to a Github Repository
2023-01-29 Moved adapters to individual folders depending on current configuration
2023-01-29 Moved WLAN to WebServer. Prevents unnecessary compiling when not required in UART mode
2023-02-02 Removed Tests. All tests were relevant to Lawicel Library. As the library has been moved, the tests are not longer relevant
2023-02-02 Removed unused ignore
2023-02-02 Fixed Websocket support
2023-02-02 Added a basic Telnet Adapter for Serial interface
2023-03-09 Activated static checks
2023-03-09 Added missing documentation
2023-03-09 Fixed documentation. Removed Doxygen-style inline comments
2023-03-09 Fixed const correctness in get functions
2023-03-09 Moved ESP32 Adapters to lib
2023-03-09 Fixed Preferences dependency
2023-03-09 Moved WS Adapter to lib
2023-03-09 Fixed dependencies after new lib organization
2023-03-09 Divided CANAdapter into header and source files
2026-03-03 Removed everything related to the webserver, as it does not currently work because of library incompatibilties
2026-03-03 Update platform and all 3rd party libs.
